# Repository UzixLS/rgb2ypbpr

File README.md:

## RGB to YPbPr simple converter

Based on "Universal RGB-to-YPbPr/Component Encoder" by Steven Hanley (thesteve)

This schematic doesn't show perfect output picture quality, but uses cheap widely available parts.

Links:

https://www.pcenginefx.com/forums/index.php?topic=13231.0

https://www.sega-16.com/forum/showthread.php?28932-Universal-RGB-to-Component-Design

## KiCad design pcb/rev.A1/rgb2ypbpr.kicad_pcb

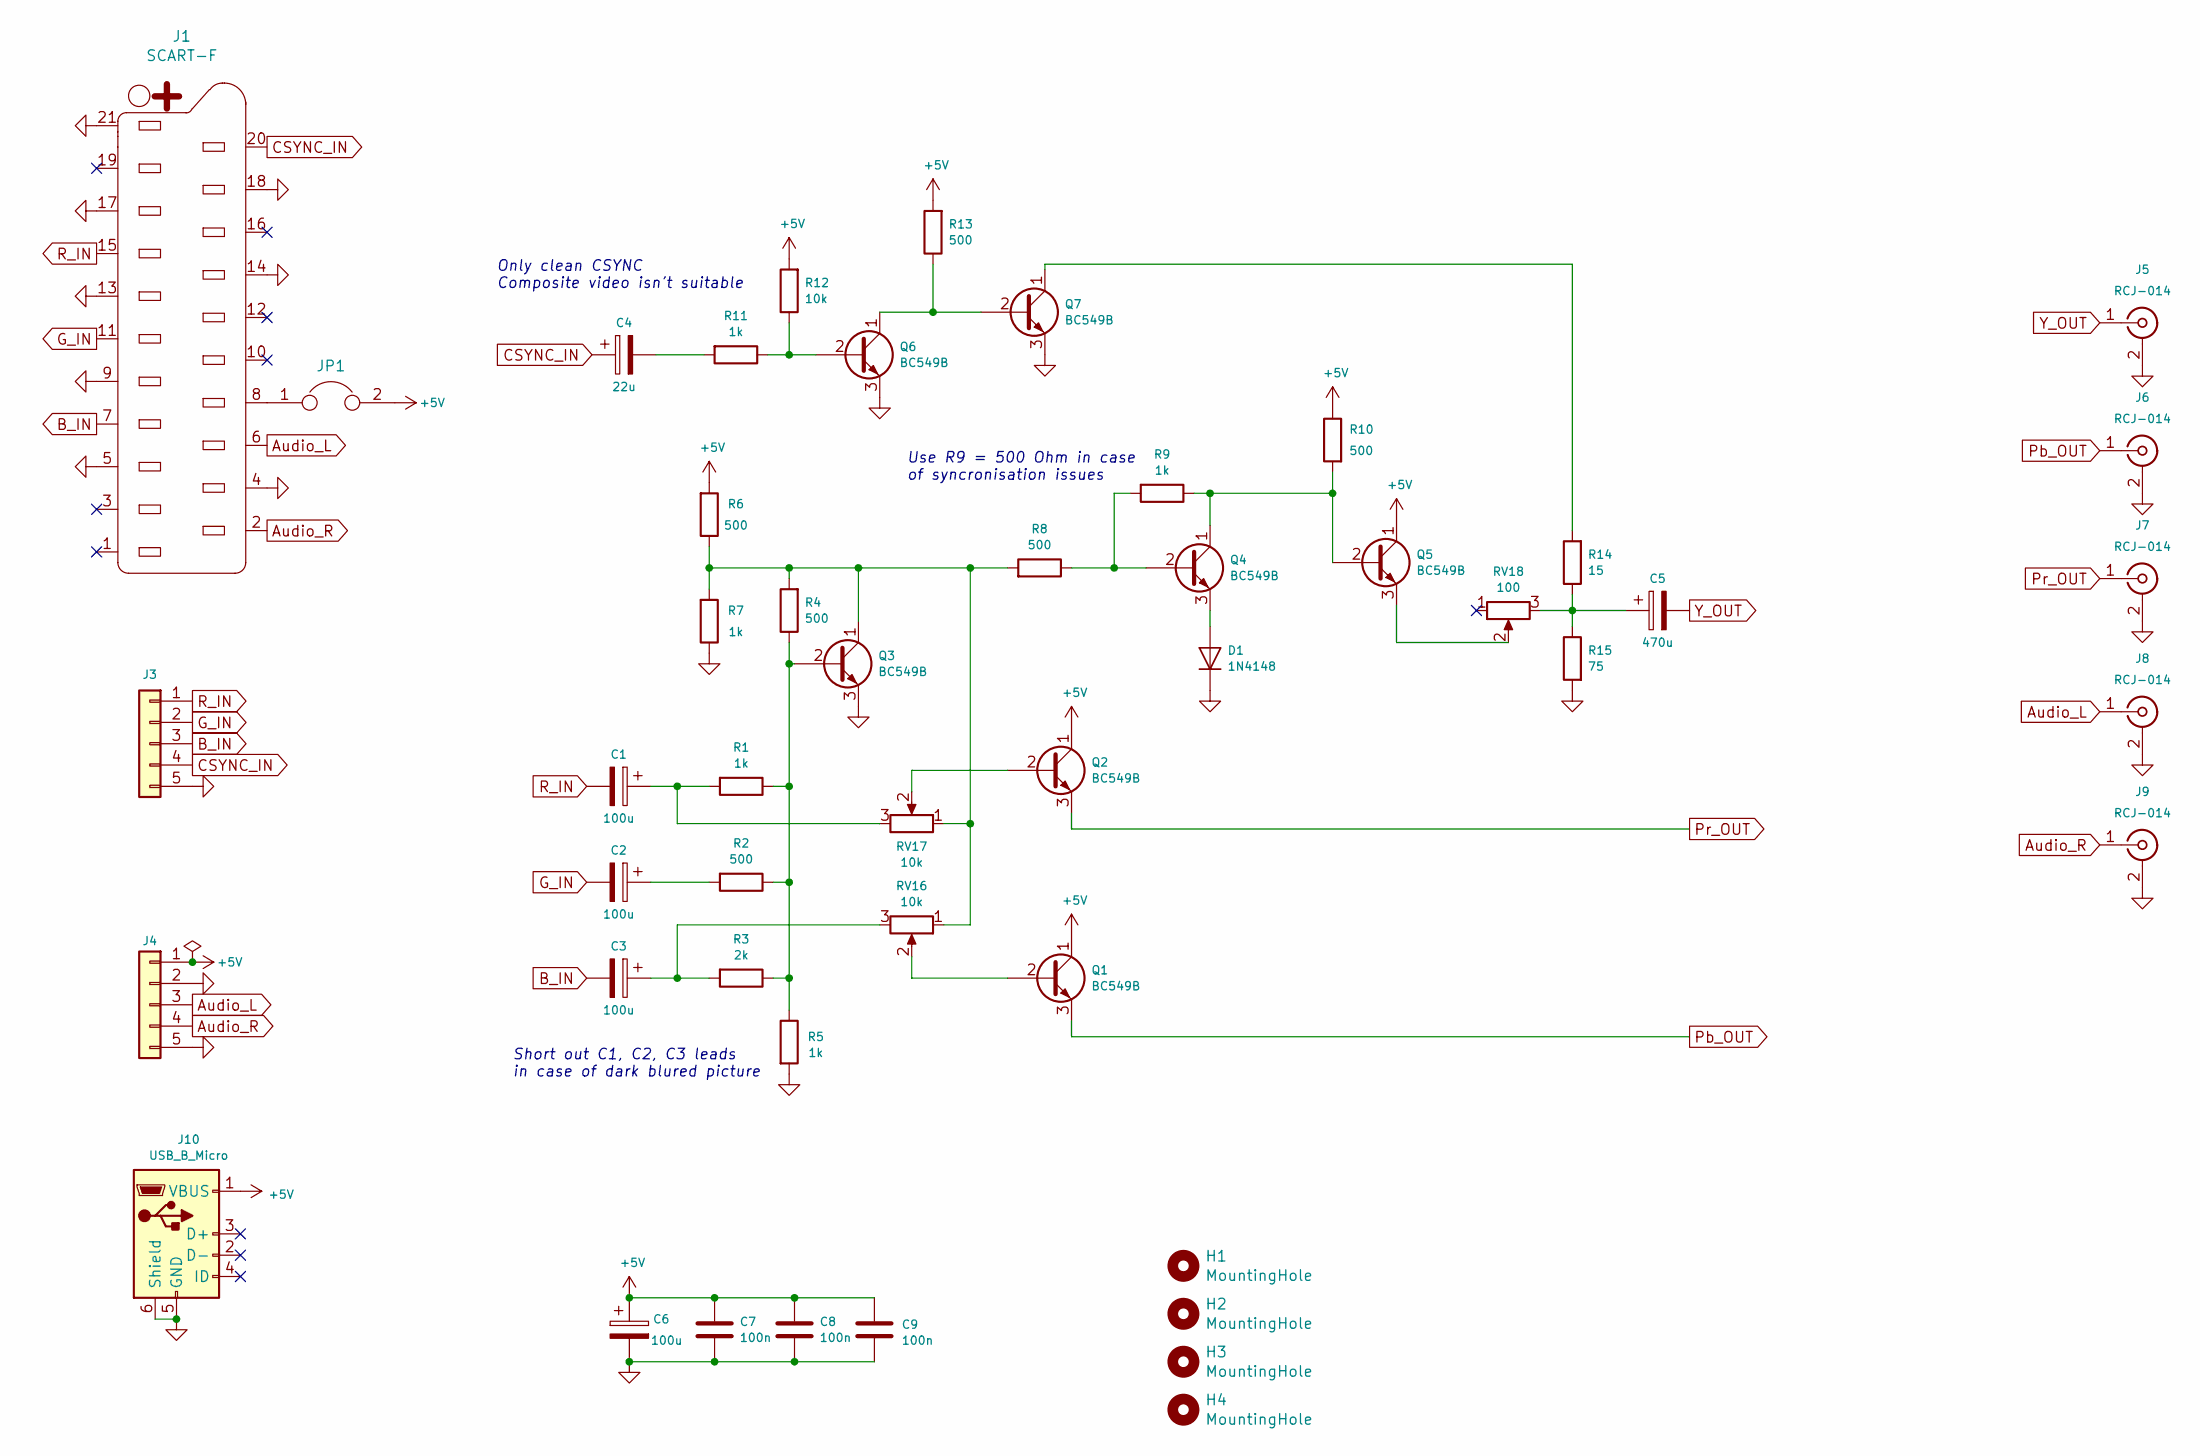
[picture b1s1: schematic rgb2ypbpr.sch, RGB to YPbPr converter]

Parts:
C1, C2, C3, C6: 100u; CP_Radial_D6.3mm_P2.50mm
C4: 22u; CP_Radial_D6.3mm_P2.50mm
C5: 470u; CP_Radial_D6.3mm_P2.50mm
C7, C8, C9: 100n; C_Disc_D7.0mm_W2.5mm_P5.00mm
D1: 1N4148; D_T-1_P10.16mm_Horizontal
H1, H2, H3, H4: MountingHole; MountingHole_3.2mm_M3
J1: SCART-F; SCART
J3: Conn_01x05; Molex_KK-254_AE-6410-05A_1x05_P2.54mm_Vertical
J4: Conn_01x03; Molex_KK-254_AE-6410-05A_1x05_P2.54mm_Vertical
J5, J6, J7, J8, J9: RCJ-014; CUI_RCJ-01X-WIDE
J10: USB_B_Micro; USB_Micro-B_Molex-105017-0001
JP1: Jumper; PinHeader_1x02_P2.54mm_Vertical
Q1, Q2, Q3, Q4, Q5, Q6, Q7: BC549B; TO-92
R1, R5, R7, R9, R11: 1k; R_Axial_DIN0207_L6.3mm_D2.5mm_P7.62mm_Horizontal
R2, R4, R6, R8, R10, R13: 500; R_Axial_DIN0207_L6.3mm_D2.5mm_P7.62mm_Horizontal
R3: 2k; R_Axial_DIN0207_L6.3mm_D2.5mm_P7.62mm_Horizontal
R12: 10k; R_Axial_DIN0207_L6.3mm_D2.5mm_P7.62mm_Horizontal
R14: 15; R_Axial_DIN0207_L6.3mm_D2.5mm_P7.62mm_Horizontal
R15: 75; R_Axial_DIN0207_L6.3mm_D2.5mm_P7.62mm_Horizontal
RV16, RV17: 10k; Potentiometer_Runtron_RM-065_Vertical
RV18: 100; Potentiometer_Runtron_RM-065_Vertical

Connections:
+5V: C6.1, C7.1, C8.1, C9.2, J4.1, J10.1 (VBUS), JP1.2, Q1.1 (C), Q2.1 (C), Q5.1 (C), R6.2, R10.1, R12.2, R13.2
Audio_L: J1.6, J4.3, J8.1 (In)
Audio_R: J1.2, J4.4, J9.1 (In)
B_IN: C3.2, J1.7, J3.3
CSYNC_IN: C4.1, J1.20, J3.4
GND: C6.2, C7.2, C8.2, C9.1, D1.1 (K), J1.4, J1.5, J1.9, J1.13, J1.14, J1.17, J1.18, J1.21, J3.5, J4.2, J4.5, J5.2 (Ext), J6.2 (Ext), J7.2 (Ext), J8.2 (Ext), J9.2 (Ext), J10.5 (GND), J10.6 (Shield), Q3.3 (E), Q6.3 (E), Q7.3 (E), R5.2, R7.1, R15.2
G_IN: C2.2, J1.11, J3.2
unnamed: C1.1, R1.2, RV17.3
unnamed: C2.1, R2.2
unnamed: C3.1, R3.2, RV16.3
unnamed: C4.2, R11.2
unnamed: C5.1, R14.1, R15.1, RV18.3
unnamed: D1.2 (A), Q4.3 (E)
unnamed: J1.8, JP1.1
unnamed: Q1.2 (B), RV16.2
unnamed: Q2.2 (B), RV17.2
unnamed: Q3.1 (C), R4.2, R6.1, R7.2, R8.2, RV16.1, RV17.1
unnamed: Q3.2 (B), R1.1, R2.1, R3.1, R4.1, R5.1
unnamed: Q4.1 (C), Q5.2 (B), R9.1, R10.2
unnamed: Q4.2 (B), R8.1, R9.2
unnamed: Q5.3 (E), RV18.2
unnamed: Q6.1 (C), Q7.2 (B), R13.1
unnamed: Q6.2 (B), R11.1, R12.1
unnamed: Q7.1 (C), R14.2
Pb_OUT: J6.1 (In), Q1.3 (E)
Pr_OUT: J7.1 (In), Q2.3 (E)
R_IN: C1.2, J1.15, J3.1
Y_OUT: C5.2, J5.1 (In)

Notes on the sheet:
Use R9 = 500 Ohm in case of syncronisation issues
Short out C1, C2, C3 leads in case of dark blured picture
Only clean CSYNC Composite video isn't suitable

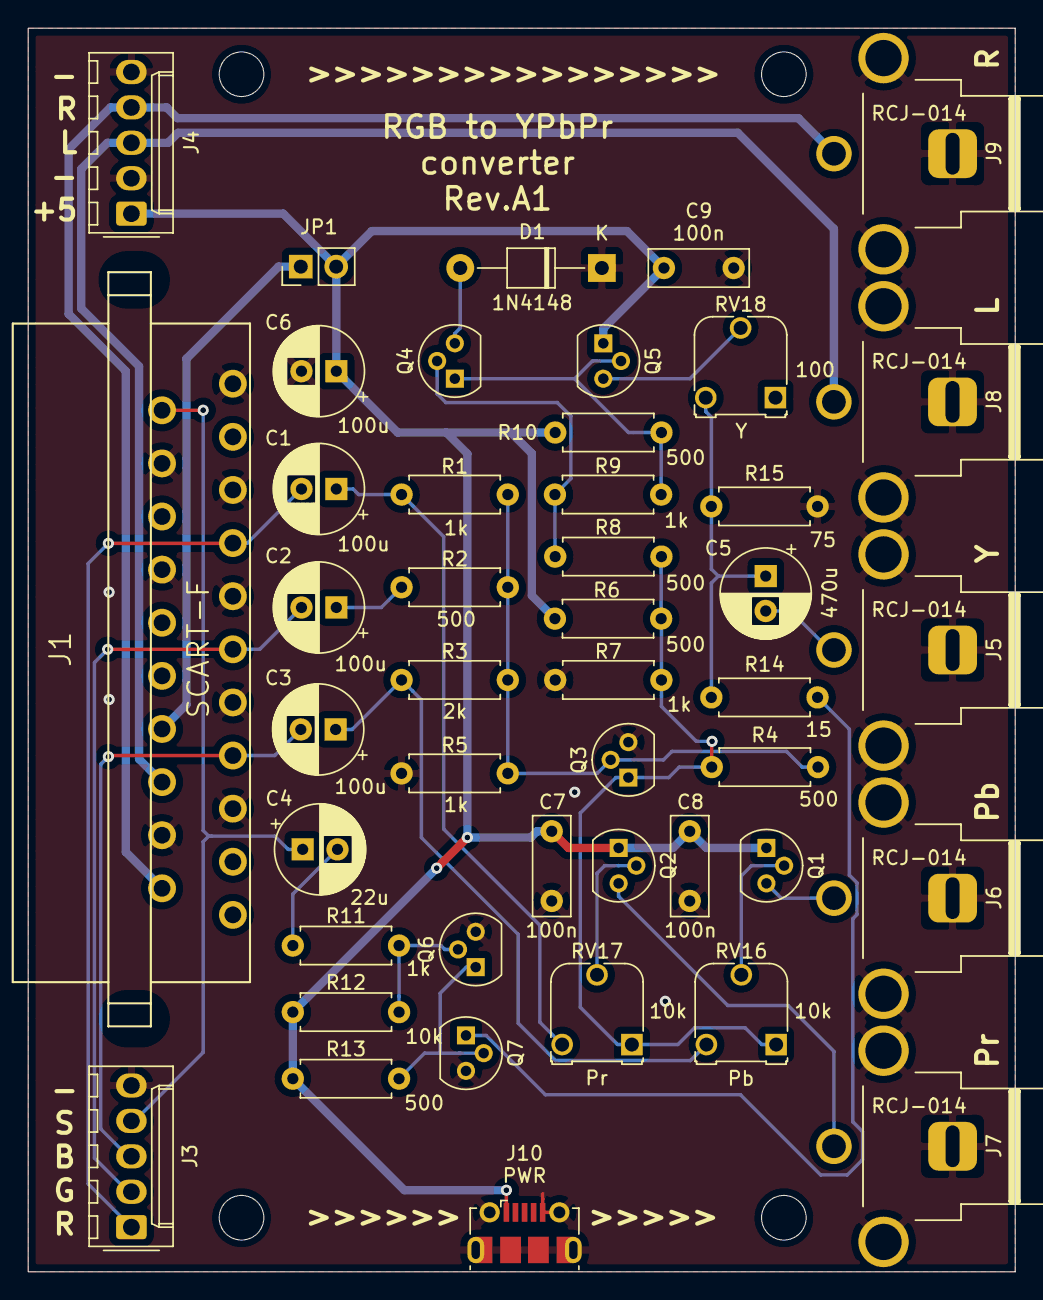
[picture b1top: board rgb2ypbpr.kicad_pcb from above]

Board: 2 copper layers, 70.8 x 89.2 mm, 49 parts (0 on the bottom side), 28 nets.

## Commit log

2020-07-29 initial
2021-01-15 add rev.A pcb
2021-01-15 add ltspice circuit
2021-01-15 add reference schemes
2021-01-15 add rev.A1 pcb
2021-01-15 update readme, add photo
2021-01-17 pcb rev.A1: replace TO-92_Inline footprint with TO-92
2021-04-08 update readme: use direct link to pcb image
2022-06-19 add license
